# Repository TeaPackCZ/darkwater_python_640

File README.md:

640 DC Motor driver
=======================

Python library based on the [Adafruit Python Library for DC + Stepper Motor HAT](https://github.com/adafruit/Adafruit-Motor-HAT-Python-Library)

#License

Designed by Dark Water. Distributed under a Creative Commons Attribution, Share-Alike license.
Development kits based on this product should be distributed under a similar license.
Commercial products using the 640 boards as a reference design need not comply with this license; further questions can be sent to team@darkwater.io.
Check license.txt for more information.

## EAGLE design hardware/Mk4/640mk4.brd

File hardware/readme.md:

Place holder for hardware file instructins

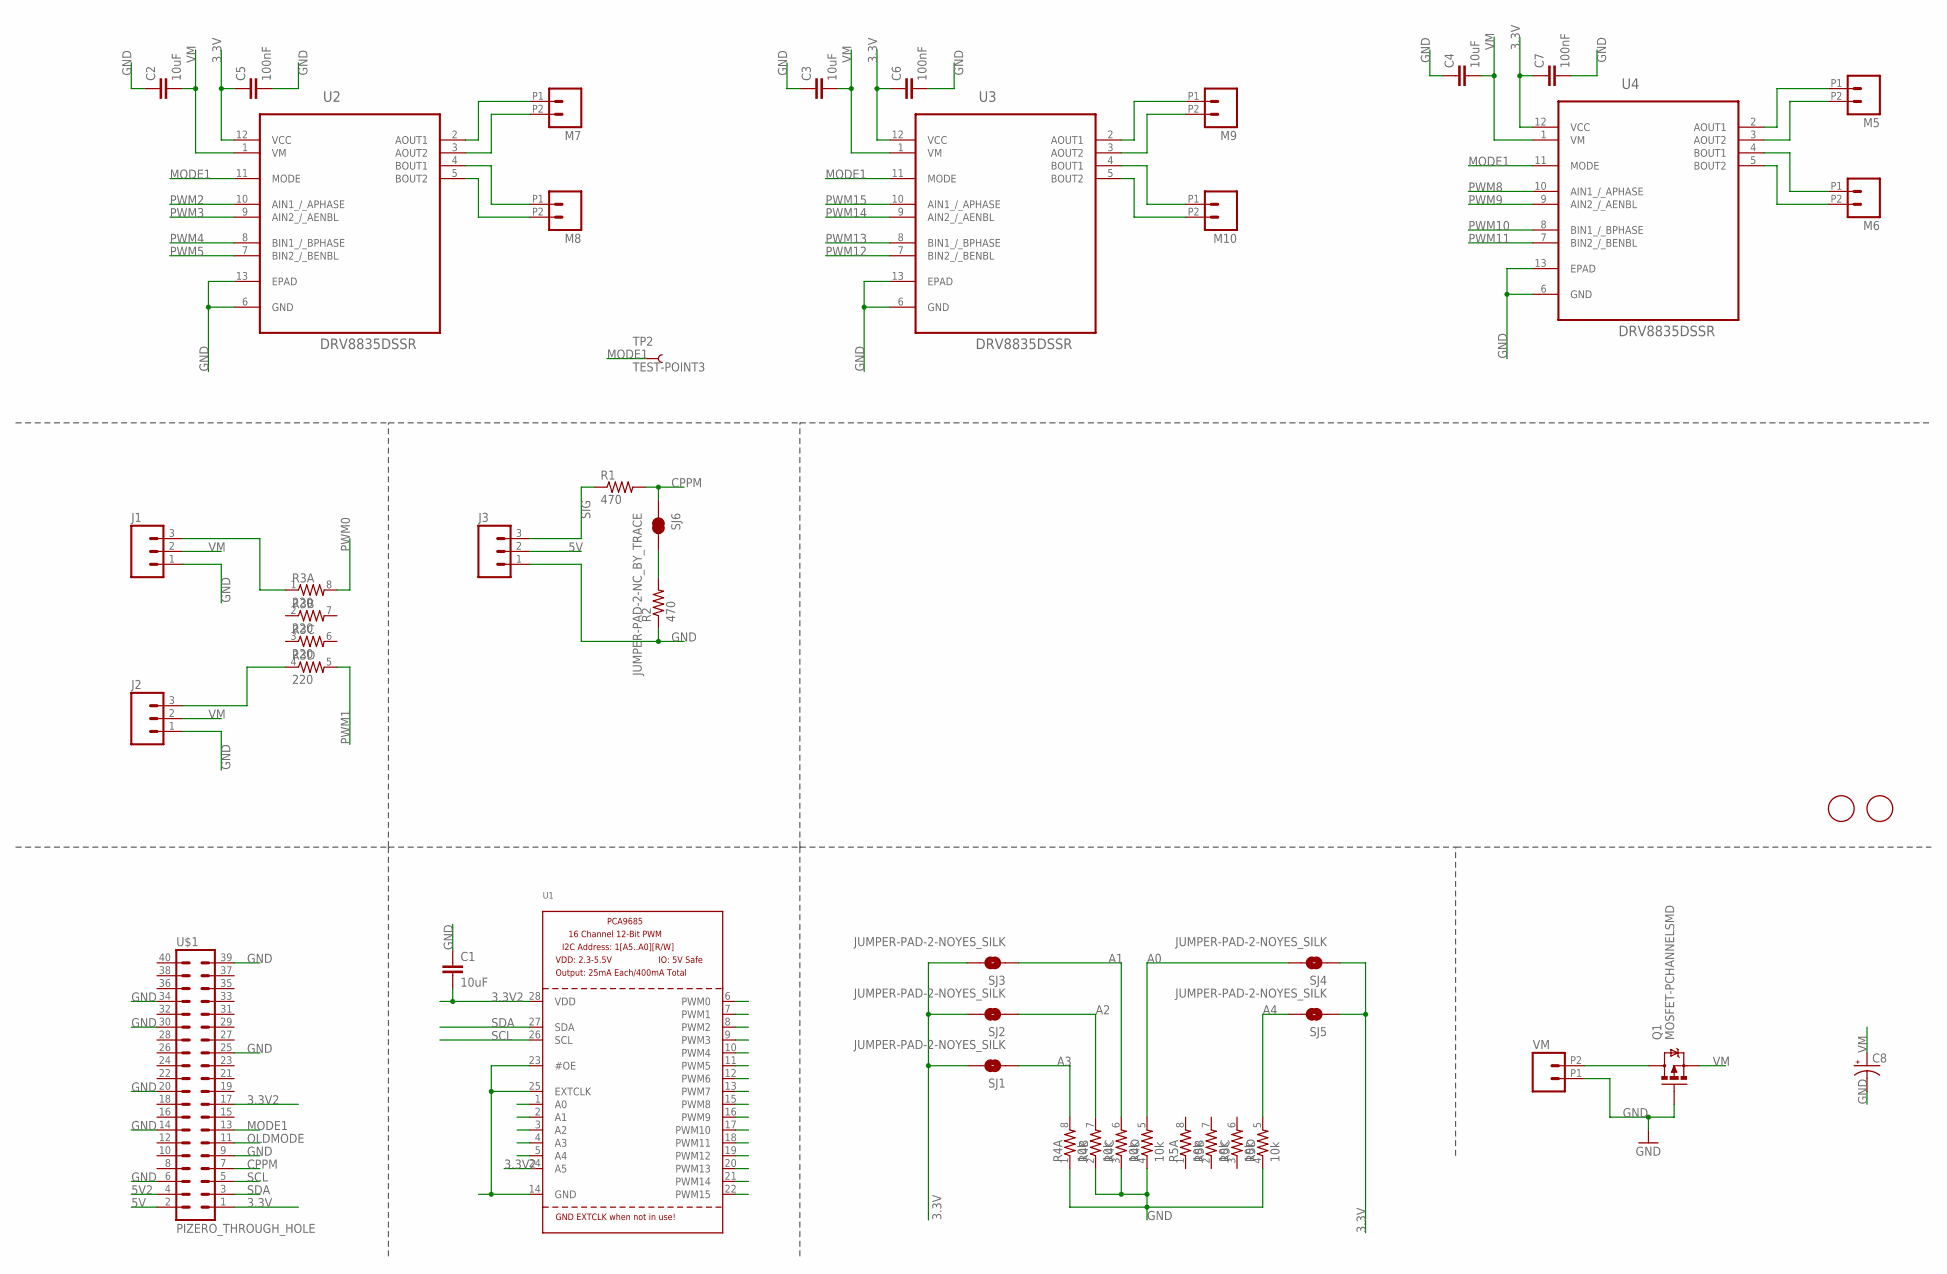
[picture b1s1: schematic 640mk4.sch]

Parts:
C1, C2, C3, C4: 10uF; 0805
C5, C6, C7: 100nF; 0805
C8: CAP_POLPTH1; CPOL-RADIAL-100UF-25V
FID1, FID2: FIDUCIAL; FIDUCIAL_1MM
J1, J2, J3: M03LOCK; 1X03_LOCK
M5, M6, M7, M8, M9, M10: M022.54MM_SCREWTERM; 1X02_2.54_SCREWTERM
Q1: MOSFET-PCHANNELSMD; SOT23-3
R1, R2: 470; 0805
R3: 220; 0603-ARV
R4, R5: 10k; 0603-ARV
SJ1, SJ2, SJ3, SJ4, SJ5: JUMPER-PAD-2-NOYES_SILK; PAD-JUMPER-2-NO_YES_SILK
SJ6: JUMPER-PAD-2-NC_BY_TRACE; PAD-JUMPER-2-NC_BY_TRACE_YES_SILK
TP2: TEST-POINT3; PAD.03X.03
U1: PCA9685; TSSOP28
U2, U3, U4: DRV8835DSSR; SON50P200X300X80-13N
U$1: PIZERO_THROUGH_HOLE; PIZERO_THOUGH_HOLE
VM: M022.54MM_SCREWTERM; 1X02_2.54_SCREWTERM

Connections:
3.3V: C5.1, C6.1, C7.1, SJ1.2, SJ2.2, SJ3.2, SJ4.1, SJ5.1, U2.12 (VCC), U3.12 (VCC), U4.12 (VCC), U$1.1
3.3V2: C1.2, U1.24 (A5), U1.28 (VDD), U$1.17
5V: J3.2, U$1.2
5V2: U$1.4
A0: R4.5 (2), SJ4.2, U1.1 (A0)
A1: R4.6 (2), SJ3.1, U1.2 (A1)
A2: R4.7 (2), SJ2.1, U1.3 (A2)
A3: R4.8 (2), SJ1.1, U1.4 (A3)
A4: R5.5 (2), SJ5.2, U1.5 (A4)
CPPM: R1.2, SJ6.1, U$1.7
GND: C1.1, C2.1, C3.1, C4.1, C5.2, C6.2, C7.2, C8.2 (-), J1.1, J2.1, J3.1, Q1.1 (G), R2.1, R4.1, R4.2 (1), R4.3 (1), R4.4 (1), R5.4 (1), U1.14 (GND), U1.23 (#OE), U1.25 (EXTCLK), U2.6 (GND), U2.13 (EPAD), U3.6 (GND), U3.13 (EPAD), U4.6 (GND), U4.13 (EPAD), U$1.6, U$1.9, U$1.14, U$1.20, U$1.25, U$1.30, U$1.34, U$1.39, VM.P1 (1)
MODE1: TP2.P$1, U2.11 (MODE), U3.11 (MODE), U4.11 (MODE), U$1.13
unnamed: R2.2, SJ6.2
unnamed: J2.3, R3.4 (1)
unnamed: J1.3, R3.1
unnamed: Q1.3 (D), VM.P2 (2)
unnamed: M6.P2 (2), U4.5 (BOUT2)
unnamed: M6.P1 (1), U4.4 (BOUT1)
unnamed: M5.P2 (2), U4.3 (AOUT2)
unnamed: M5.P1 (1), U4.2 (AOUT1)
unnamed: M8.P2 (2), U2.5 (BOUT2)
unnamed: M8.P1 (1), U2.4 (BOUT1)
unnamed: M7.P2 (2), U2.3 (AOUT2)
unnamed: M7.P1 (1), U2.2 (AOUT1)
unnamed: M10.P2 (2), U3.5 (BOUT2)
unnamed: M10.P1 (1), U3.4 (BOUT1)
unnamed: M9.P2 (2), U3.3 (AOUT2)
unnamed: M9.P1 (1), U3.2 (AOUT1)
OLDMODE: U$1.11
PWM0: R3.8 (2), U1.6 (PWM0)
PWM1: R3.5 (2), U1.7 (PWM1)
PWM2: U1.8 (PWM2), U2.10 (AIN1_/_APHASE)
PWM3: U1.9 (PWM3), U2.9 (AIN2_/_AENBL)
PWM4: U1.10 (PWM4), U2.8 (BIN1_/_BPHASE)
PWM5: U1.11 (PWM5), U2.7 (BIN2_/_BENBL)
PWM6: U1.12 (PWM6)
PWM7: U1.13 (PWM7)
PWM8: U1.15 (PWM8), U4.10 (AIN1_/_APHASE)
PWM9: U1.16 (PWM9), U4.9 (AIN2_/_AENBL)
PWM10: U1.17 (PWM10), U4.8 (BIN1_/_BPHASE)
PWM11: U1.18 (PWM11), U4.7 (BIN2_/_BENBL)
PWM12: U1.19 (PWM12), U3.7 (BIN2_/_BENBL)
PWM13: U1.20 (PWM13), U3.8 (BIN1_/_BPHASE)
PWM14: U1.21 (PWM14), U3.9 (AIN2_/_AENBL)
PWM15: U1.22 (PWM15), U3.10 (AIN1_/_APHASE)
SCL: U1.26 (SCL), U$1.5
SDA: U1.27 (SDA), U$1.3
SIG: J3.3, R1.1
VM: C2.2, C3.2, C4.2, C8.1 (+), J1.2, J2.2, Q1.2 (S), U2.1 (VM), U3.1 (VM), U4.1 (VM)

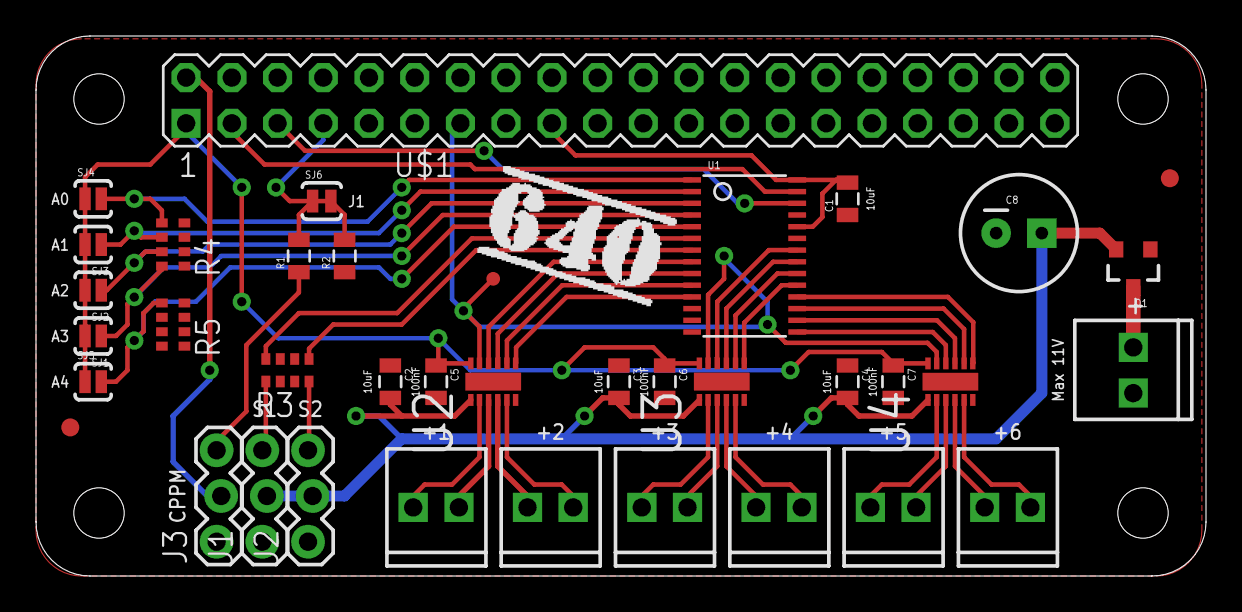
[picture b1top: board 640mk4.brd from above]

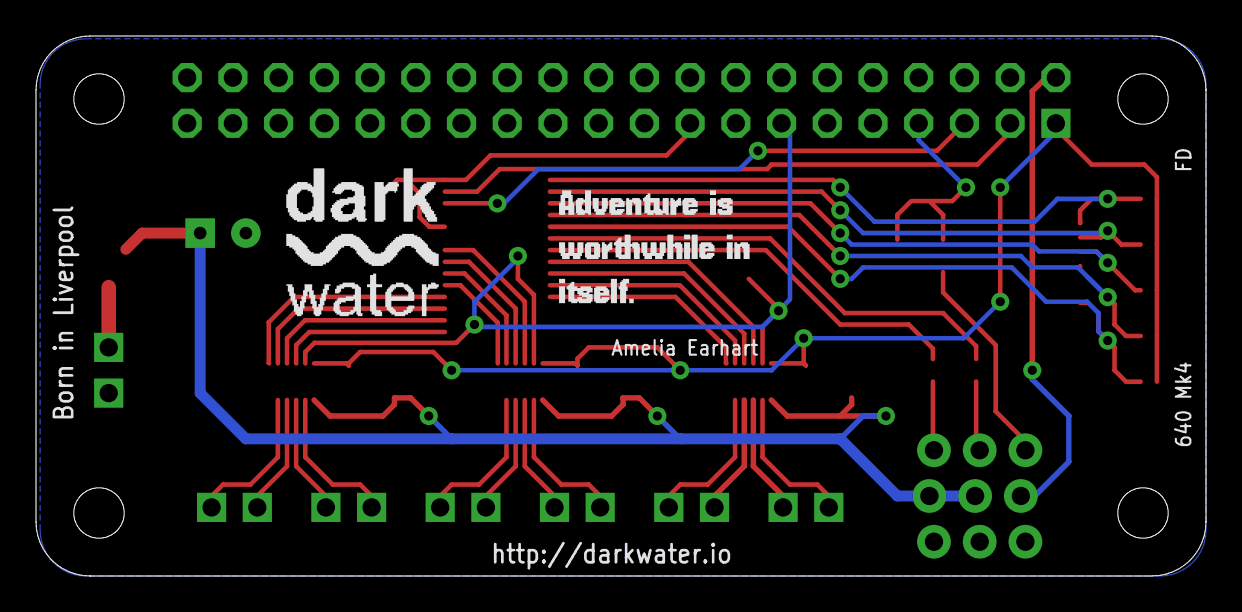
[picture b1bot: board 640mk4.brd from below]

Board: 2 copper layers, 65.0 x 30.0 mm, 41 parts (2 on the bottom side), 45 nets.

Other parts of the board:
U$4: DARKWATER
U$5: ADVENTURE
U$6: 640SMALL

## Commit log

2016-02-13 Rejig ready for code updates
2016-02-13 remove old
2016-02-13 Remove stepper for now
2016-02-14 bit more work on classes
2016-02-21 New updates for testing
2016-02-21 New class and New example
2016-02-28 Updated for Mk2
2016-02-28 Removed Mk1
2016-04-03 Added updates for getPWM and correctionFactor
2016-04-03 Brought inline with escape code
2016-04-30 Updated for mk3
2016-04-30 shorten test
2016-04-30 Change structure
2016-04-30 readme files
2016-07-02 Added hardware directory
2016-07-08 Mk4 hardware files
2016-07-08 Added CC
2016-08-13 Got rid of non-python files
2016-08-13 Update to code
    Needs testing
2016-08-13 change to method names
2016-08-15 Moved example code
2016-08-15 changed methods
2016-08-15 update test
2016-08-15 bug fix - indents
2016-08-15 frequency change
2016-08-15 added math
2016-08-15 Updated test script
2016-08-15 updated for servos
2016-08-15 debug
2016-08-15 test update
2016-08-15 debug servo code
2016-08-15 change frequency
2016-08-15 updated test
2016-08-15 added correction factor
2016-08-15 A few changes
    Added correction factor
    Change motor test code
2016-08-23 updated for new boards
2016-08-23 changed mode pin
2016-08-23 changed pin for new boards
2016-09-12 quick update test
2016-09-12 hide stepper for now
2016-09-12 stepper hide for testing
2016-09-13 stepper library testing
2016-09-13 indentation
2016-09-13 more indents
2016-09-13 stepper test
2016-09-13 oops
2016-09-13 remove pwm
2016-09-13 rejig
2016-09-17 New motor code to handle IN/IN mode
2016-09-17 updated stepper
2016-09-17 dodgy c synatx in there :)
2016-09-17 setmode bug
2016-09-17 release bug
2016-09-17 mode fix
2016-09-17 another test
2016-09-18 removed debug prints
2016-09-18 more debug stuff
2016-09-18 quick import test
2016-09-18 change print statements
2016-09-18 missed a print
2016-09-25 changed function name for stepper speed
2016-09-29 updating for python 3
2016-09-29 test script update
2016-09-29 removed dodgy .
2016-09-29 grrr
2016-09-29 remove legacy
2016-09-29 back update
2016-09-29 typo
2016-09-29 servo update
2016-09-29 initial imu
2016-09-29 python3 prints
2016-10-04 quick code test
2016-10-04 redo examples
2016-10-04 messages on stepper example
2016-10-17 changed release code
2016-10-17 change version
2018-05-22 Add RaspberryPi Zero BCM version

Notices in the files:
parts and their libraries:
SparkFun-Connectors: Licensing: Creative Commons ShareAlike 4.0 International - https://creativecommons.org/licenses/by-sa/4.0
